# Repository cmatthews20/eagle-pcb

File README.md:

# PCB
Files and Libraries associated with my Autodesk Eagle/Fusion360 PCB project

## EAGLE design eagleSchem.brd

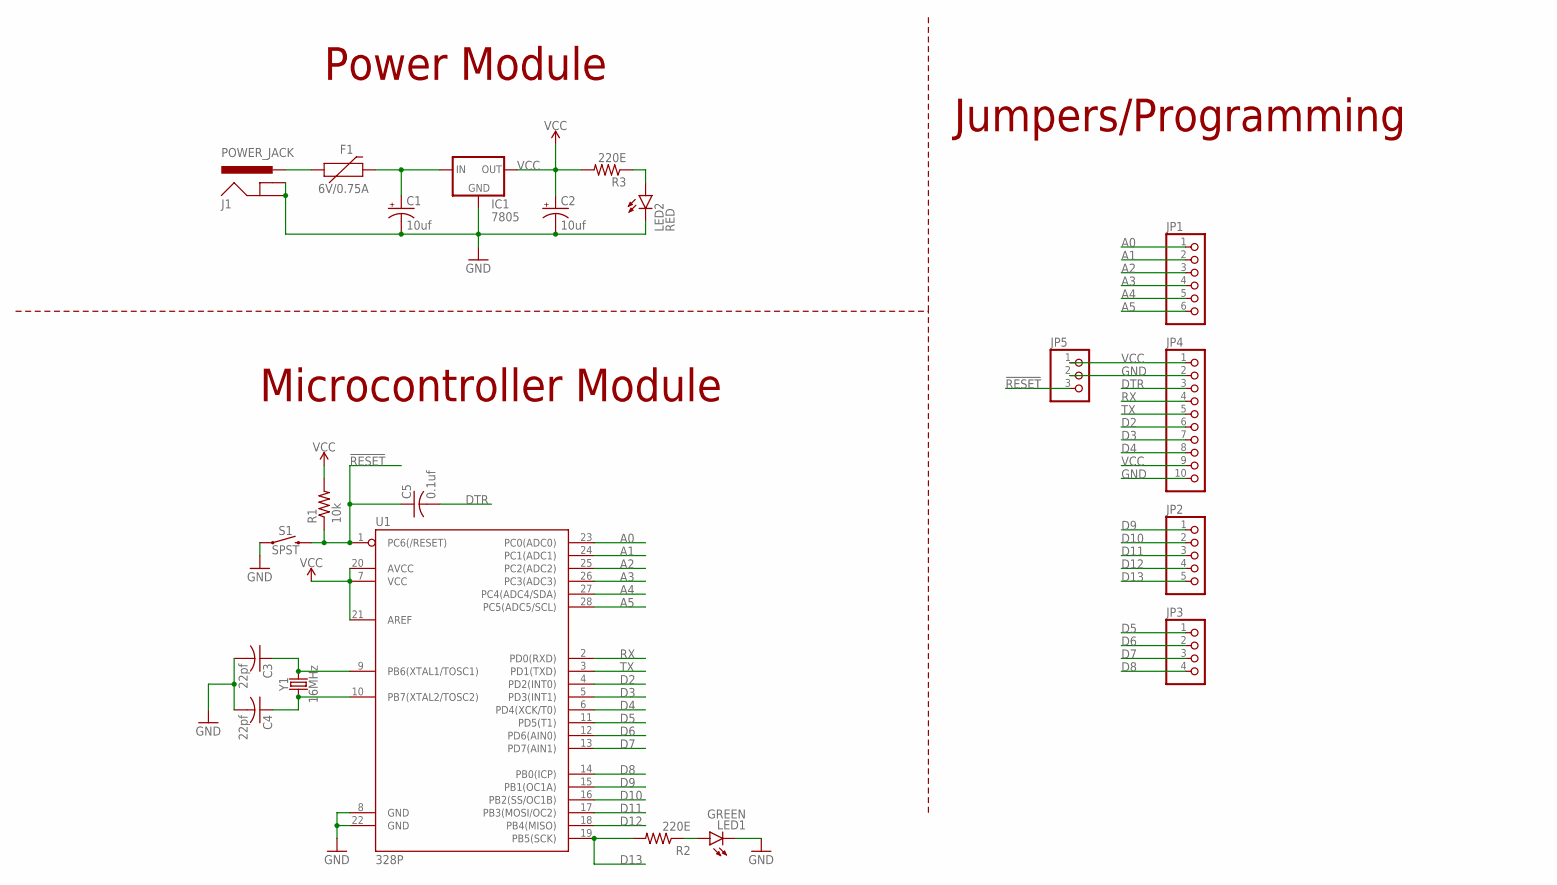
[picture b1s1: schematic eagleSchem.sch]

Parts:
C1, C2: 10uf; E2,5-6
C3, C4: 22pf; C025-024X044
C5: 0.1uf; C025-024X044
F1: 6V/0.75A; 1206
IC1: 7805; 78XXS
J1: POWER_JACK; POWER_JACK_PTH
JP1: PINHD-1X6; 1X06
JP2: PINHD-1X5; 1X05
JP3: PINHD-1X4; 1X04
JP4: PINHD-1X10; 1X10
JP5: PINHD-1X3; 1X03
LED1: GREEN; LED3MM
LED2: RED; LED3MM
R1: 10k; 0204/7
R2, R3: 220E; 0204/7
S1: SPST; TACTILE_SWITCH_PTH_6.0MM
U1: 328P; DIP28
Y1: 16MHz; HC49US

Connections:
!RESET: C5.1, JP5.3, R1.1, S1.3 (2), U1.1 (PC6(/RESET))
A0: JP1.1, U1.23 (PC0(ADC0))
A1: JP1.2, U1.24 (PC1(ADC1))
A2: JP1.3, U1.25 (PC2(ADC2))
A3: JP1.4, U1.26 (PC3(ADC3))
A4: JP1.5, U1.27 (PC4(ADC4/SDA))
A5: JP1.6, U1.28 (PC5(ADC5/SCL))
D2: JP4.6, U1.4 (PD2(INT0))
D3: JP4.7, U1.5 (PD3(INT1))
D4: JP4.8, U1.6 (PD4(XCK/T0))
D5: JP3.1, U1.11 (PD5(T1))
D6: JP3.2, U1.12 (PD6(AIN0))
D7: JP3.3, U1.13 (PD7(AIN1))
D8: JP3.4, U1.14 (PB0(ICP))
D9: JP2.1, U1.15 (PB1(OC1A))
D10: JP2.2, U1.16 (PB2(SS/OC1B))
D11: JP2.3, U1.17 (PB3(MOSI/OC2))
D12: JP2.4, U1.18 (PB4(MISO))
D13: JP2.5, R2.2, U1.19 (PB5(SCK))
DTR: C5.2, JP4.3
GND: C1.-, C2.-, C3.2, C4.2, IC1.GND, J1.GND, J1.GNDBREAK, JP4.2, JP4.10, JP5.2, LED1.K (C), LED2.K (C), S1.1, U1.8 (GND), U1.22 (GND)
unnamed: C1.+, F1.2, IC1.IN
unnamed: C3.1, U1.9 (PB6(XTAL1/TOSC1)), Y1.2
unnamed: C4.1, U1.10 (PB7(XTAL2/TOSC2)), Y1.1
unnamed: LED2.A, R3.1
unnamed: LED1.A, R2.1
unnamed: F1.1, J1.PWR
RX: JP4.4, U1.2 (PD0(RXD))
TX: JP4.5, U1.3 (PD1(TXD))
VCC: C2.+, IC1.OUT, JP4.1, JP4.9, JP5.1, R1.2, R3.2, U1.7 (VCC), U1.20 (AVCC), U1.21 (AREF)

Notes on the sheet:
Power Module
Jumpers/Programming
Microcontroller Module

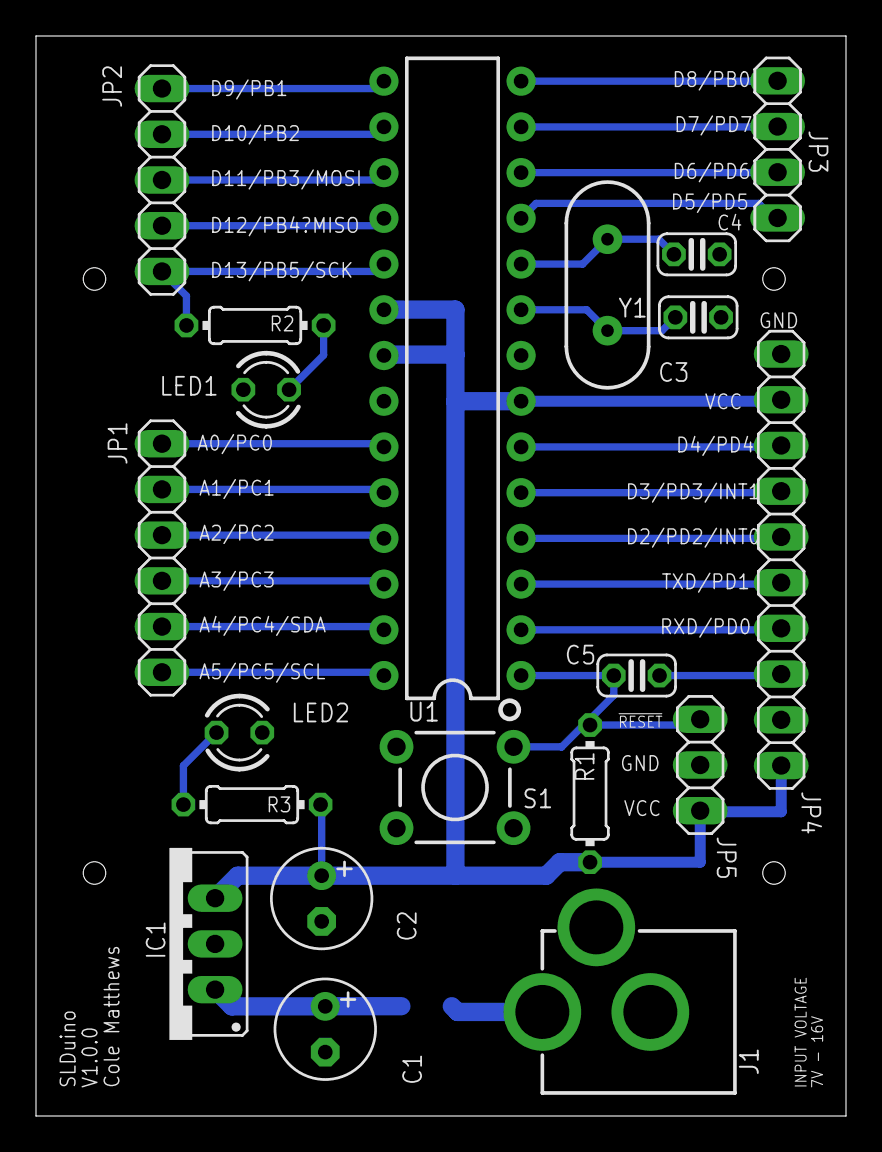
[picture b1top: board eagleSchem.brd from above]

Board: 2 copper layers, 45.0 x 60.0 mm, 21 parts (1 on the bottom side), 30 nets.

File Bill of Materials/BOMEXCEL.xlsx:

Qty | Value | Device | Package | Parts | Description | POPULARITY | PROD_ID | SF_ID | SF_SKU | SPICEPREFIX | VALUE | MPN (Generic part if not listed)
1 |  | PINHD-1X10 | 1X10 | JP4 | PIN HEADER | 35
1 |  | PINHD-1X3 | 1X03 | JP5 | PIN HEADER | 92
1 |  | PINHD-1X4 | 1X04 | JP3 | PIN HEADER | 91
1 |  | PINHD-1X5 | 1X05 | JP2 | PIN HEADER | 69
1 |  | PINHD-1X6 | 1X06 | JP1 | PIN HEADER | 79
1 | 0.1uf | C-US025-024X044 | C025-024X044 | C5 | CAPACITOR, American symbol | 17 |  |  |  | C
1 | 10k | R-US_0204/7 | 0204/7 | R1 | RESISTOR, American symbol | 48 |  |  |  | R
2 | 10uf | CPOL-USE2.5-6 | E2,5-6 | C1, C2 | POLARIZED CAPACITOR, American symbol | 14 |  |  |  | C
1 | 16MHz | CRYSTAL-16MHZPTH-HC49US | HC49US | Y1 | 16MHz Crystal |  | XTAL-08181 | COM-00536 |  |  | 16MHz
2 | 220E | R-US_0204/7 | 0204/7 | R2, R3 | RESISTOR, American symbol | 48 |  |  |  | R
2 | 22pf | C-US025-024X044 | C025-024X044 | C3, C4 | CAPACITOR, American symbol | 17 |  |  |  | C
1 | 328P | ATMEGA328P_PDIP | DIP28 | U1 | Atmel 328P |  | IC-09136 |  |  |  | 328P | ATMEGA328P-PU
1 | 6V/0.75A | PPTC_0.75A | 1206 | F1 | Resettable Fuse PPTC |  | RES-11150 |  |  |  | 6V/0.75A
1 | 7805 | 78XXS | 78XXS | IC1 | VOLTAGE REGULATOR | 18
1 | GREEN | LED3MM | LED3MM | LED1 | LED | 97
1 | POWER_JACK | POWER_JACK | POWER_JACK_PTH | J1 | Power Jack Connector |  | CONN-08197
1 | RED | LED3MM | LED3MM | LED2 | LED | 97
1 | SPST | MOMENTARY-SWITCH-SPST-PTH-6.0MM | TACTILE_SWITCH_PTH_6.0MM | S1 | Momentary Switch (Pushbutton) - SPST |  | SWCH-08441 |  | COM-00097

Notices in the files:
parts and their libraries:
SparkFun-Connectors: Licensing: Creative Commons ShareAlike 4.0 International - https://creativecommons.org/licenses/by-sa/4.0
